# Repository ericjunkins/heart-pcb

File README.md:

# heart-pcb

## Project Information
Heart PCB is a device that uses a STM8S003K3 Microchip to do bit-level control of a set of LEDs to display an input message in half-byte binary

### Software utilites
#### STM8S003K3 Programming

Programming of the STM8S003K3 was done using ST Visual Develop (STVD) and utilized ST Visual Programming (STVP). In addition it requires the Cosmic Compilier software.

> https://www.st.com/en/development-tools/stvd-stm8.html

> https://www.st.com/content/st_com/en/products/development-tools/software-development-tools/stm8-software-development-tools/stm8-programmers/stvp-stm8.html

> http://www.cosmicsoftware.com/download.php

I initially followed along with the STM8SVLDISCOVERY discovery board tutorial to program the STM8S003K3

> https://www.st.com/content/ccc/resource/technical/document/user_manual/53/20/92/c8/ad/57/45/e8/DM00040678.pdf/files/DM00040678.pdf/jcr:content/translations/en.DM00040678.pdf

#### PCB Development

The printed circuit board was designed using KiCAD, the Gerber files can be found at 

> [Gerber File Location](Gerbers/)

## Technical Information
### PCB Development

#### Electrical Schematic 

#### PCB Board Layout

### Software Development

The STM8S003K3 MCU is programmed to blink the 4 display LEDS(2-5) to display a message in half-bit binary at 0.5 Hz frequency. Below is an explaination on how it does this.

* Loop through the char * message and look at each individual char. 
* Each char is an 8 bit sequence, which will first be broken down into a "high byte" and "low byte". These are really a high half-byte and low half-byte as they are only 4 bits each. 
* The high byte and low byte will be switched, because humans read binary starting at the 0th bit, which is the right most bit, so we will want to switch high/low to make more sense to us
* These are now inserted into a bitArray, which is of length 2*length(message)

* Once the bitArray is fully built it proceeds to the main loop of LED control
* Each element of the bitArray is taken and each individual bit is then used to turn on/off an LED. Again because humans read right o left the LED1 (left-most on the PCB) corresponds to bit0, and LED4 (right-most on the PCB) corresponds to bit3

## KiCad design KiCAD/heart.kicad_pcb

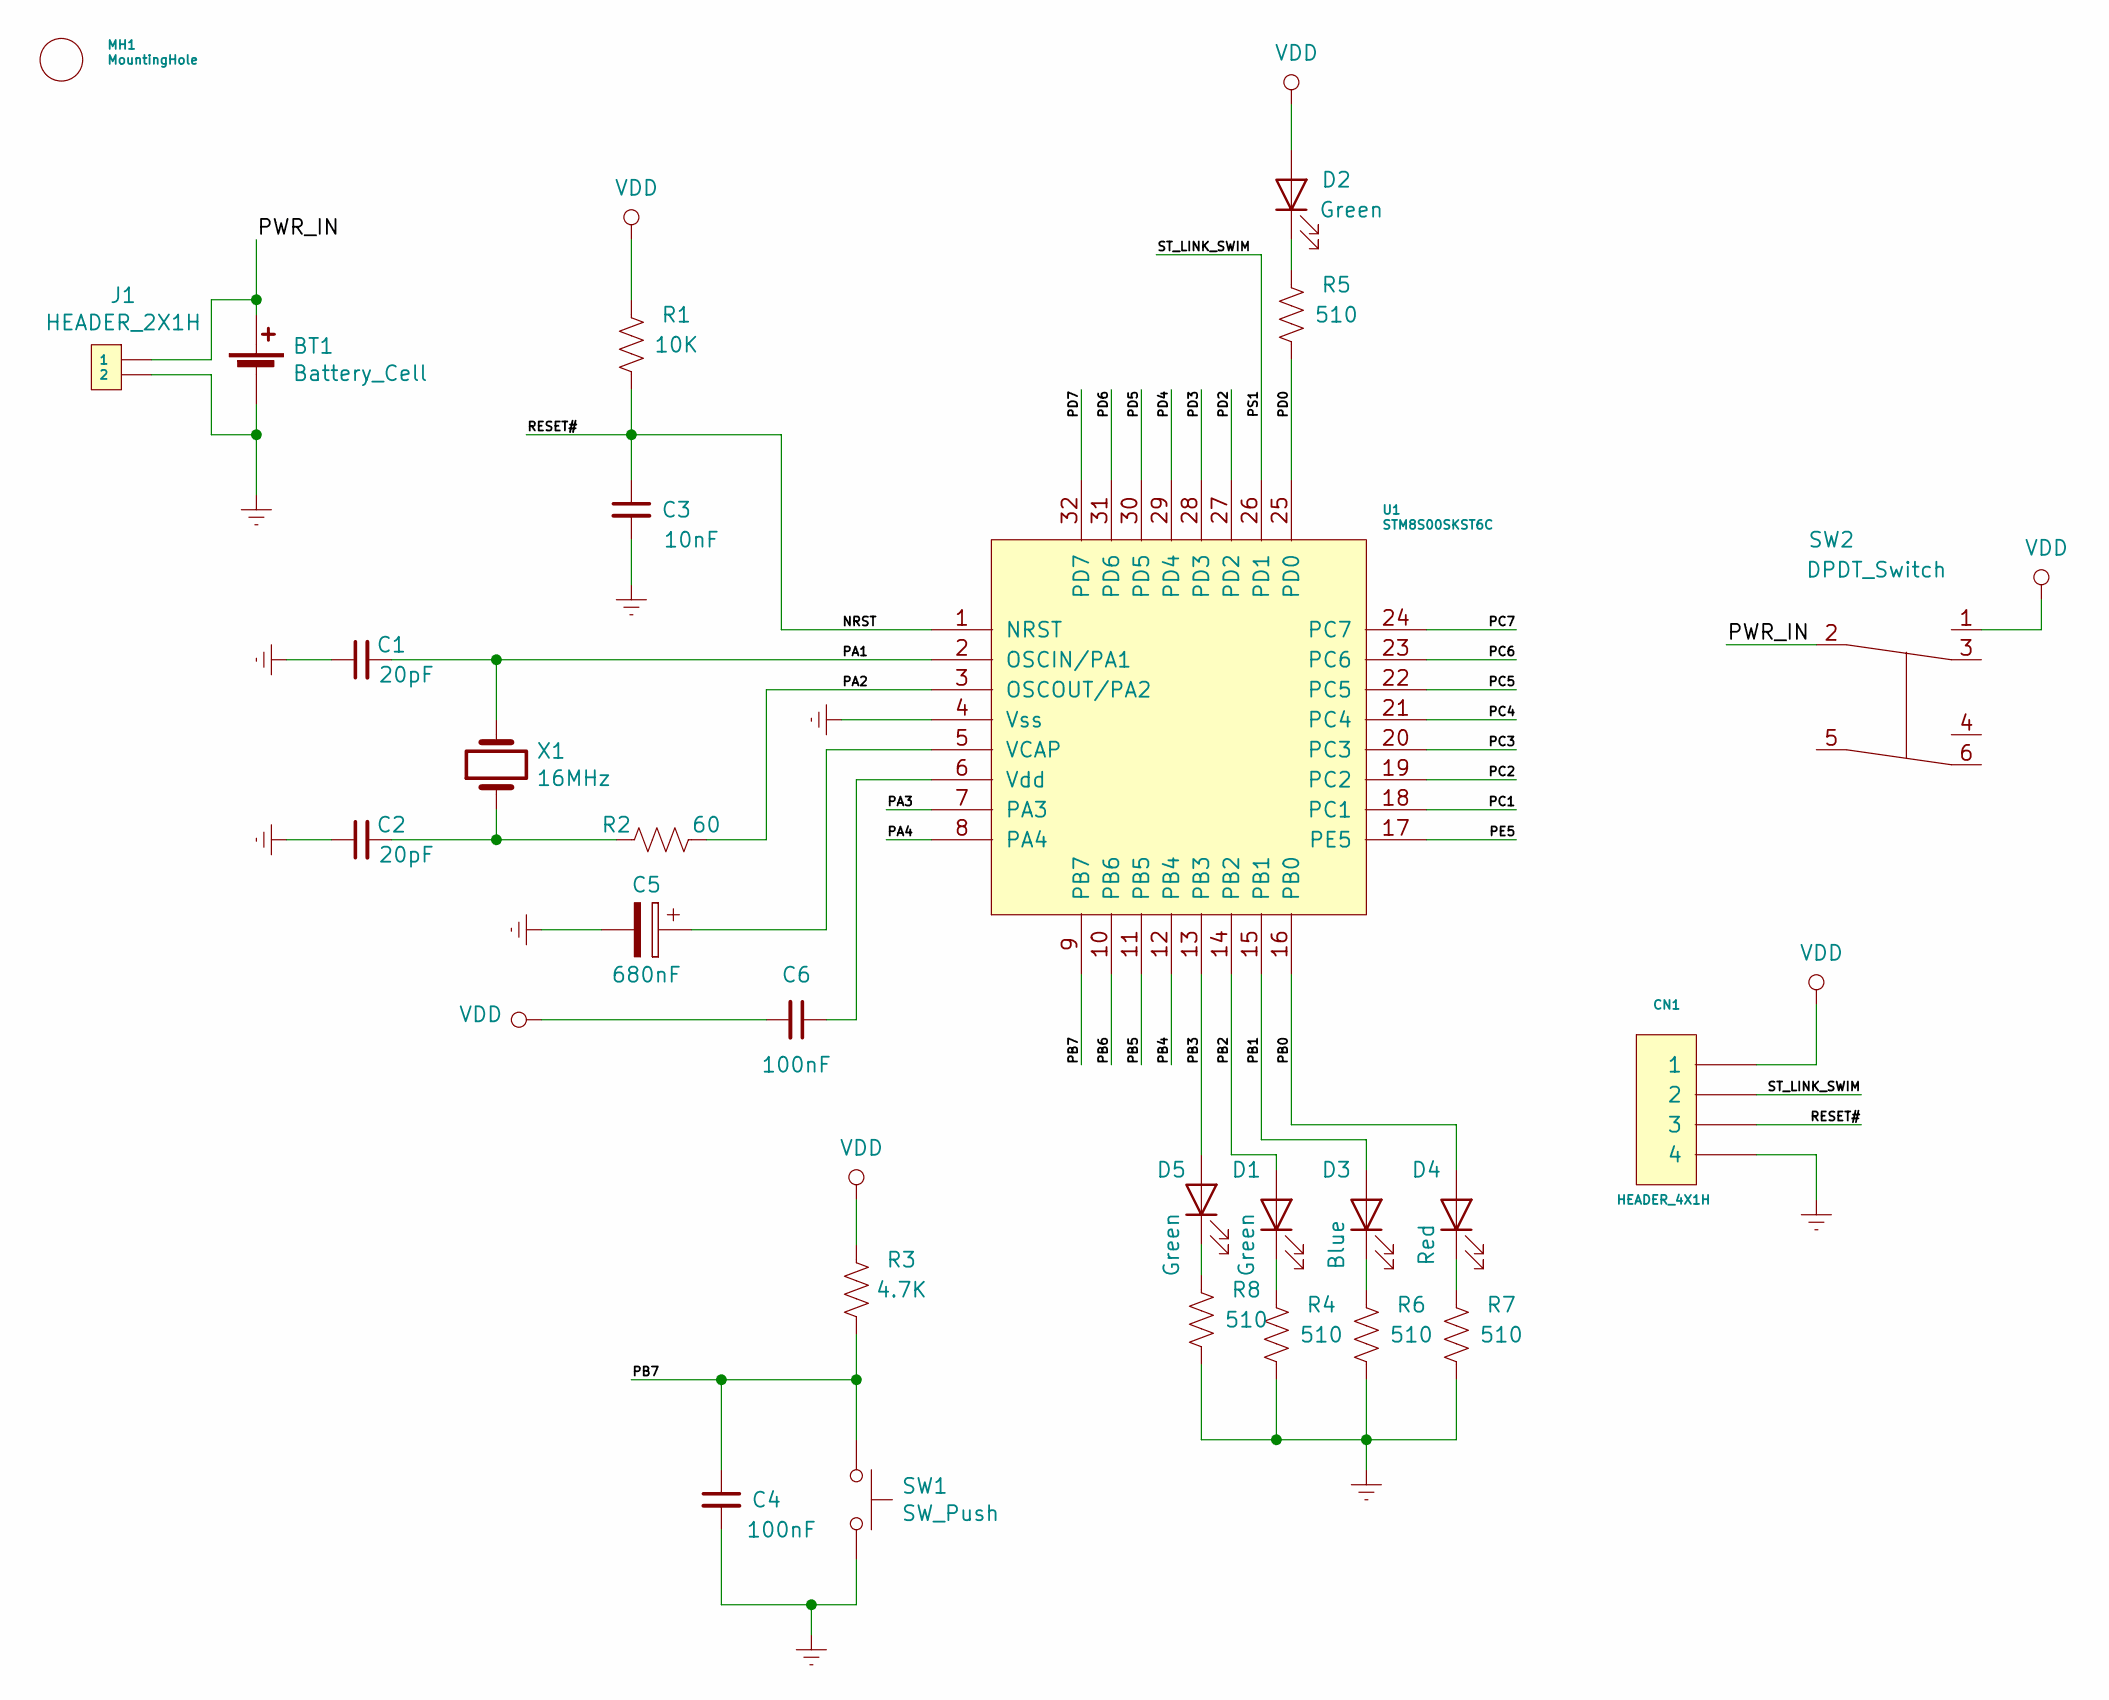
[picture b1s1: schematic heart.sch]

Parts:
BT1: Battery_Cell; SMD 12MM Coin Battery Retainer
C1, C2: 20pF; C_0805_2012Metric
C3: 10nF; C_0805_2012Metric
C4, C6: 100nF; C_0805_2012Metric
C5: 680nF; CP_Elec_6.3x5.9
CN1: HEADER_4X1H
D1, D2, D5: Green; LED_0805_2012Metric
D3: Blue; LED_0805_2012Metric
D4: Red; LED_0805_2012Metric
J1: HEADER_2X1H
MH1: MountingHole; keychain_hole
R1: 10K; R_0805_2012Metric
R2: 60; R_0805_2012Metric
R3: 4.7K; R_0805_2012Metric
R4, R5, R6, R7, R8: 510; R_0805_2012Metric
SW1: SW_Push; HEADER_2X1H
SW2: DPDT_Switch; 732-10145-1-ND DPDT Slide Switch
U1: STM8S00SKST6C; LQFP-32_7x7mm_P0.8mm
X1: 16MHz; Crystal_SMD_HC49-SD

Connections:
/NRST: C3.1, CN1.3, R1.1, U1.1 (NRST)
/PA1: C1.2, U1.2 (OSCIN/PA1), X1.2
/PA2: R2.2, U1.3 (OSCOUT/PA2)
/PA3: U1.7 (PA3)
/PA4: U1.8 (PA4)
/PB0: D4.2 (A), U1.16 (PB0)
/PB1: D3.2 (A), U1.15 (PB1)
/PB2: D1.2 (A), U1.14 (PB2)
/PB3: D5.2 (A), U1.13 (PB3)
/PB4: U1.12 (PB4)
/PB5: U1.11 (PB5)
/PB6: U1.10 (PB6)
/PB7: C4.1, R3.1, SW1.1, U1.9 (PB7)
/PC1: U1.18 (PC1)
/PC2: U1.19 (PC2)
/PC3: U1.20 (PC3)
/PC4: U1.21 (PC4)
/PC5: U1.22 (PC5)
/PC6: U1.23 (PC6)
/PC7: U1.24 (PC7)
/PD0: R5.1, U1.25 (PD0)
/PD2: U1.27 (PD2)
/PD3: U1.28 (PD3)
/PD4: U1.29 (PD4)
/PD5: U1.30 (PD5)
/PD6: U1.31 (PD6)
/PD7: U1.32 (PD7)
/PE5: U1.17 (PE5)
/PS1: CN1.2, U1.26 (PD1)
/PWR_IN: BT1.1 (+), J1.1, SW2.2
Earth: BT1.2 (-), C1.1, C2.1, C3.2, C4.2, C5.2, CN1.4, J1.2, R4.1, R6.1, R7.1, R8.1, SW1.2, U1.4 (Vss)
unnamed: C2.2, R2.1, X1.1
unnamed: C5.1, U1.5 (VCAP)
unnamed: C6.1, U1.6 (Vdd)
unnamed: D1.1 (K), R4.2
unnamed: D2.1 (K), R5.2
unnamed: D3.1 (K), R6.2
unnamed: D4.1 (K), R7.2
unnamed: D5.1 (K), R8.2
VDD: C6.2, CN1.1, D2.2 (A), R1.2, R3.2, SW2.1

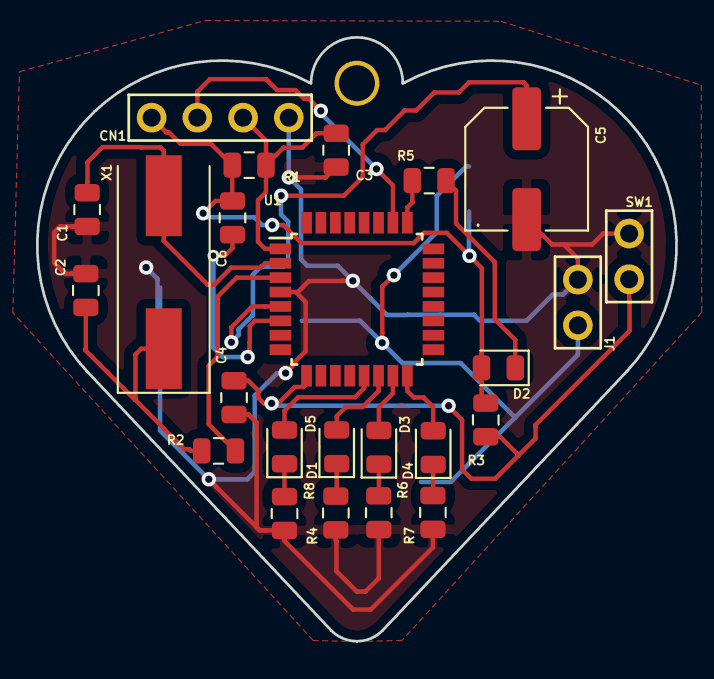
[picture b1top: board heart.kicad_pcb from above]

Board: 2 copper layers, 35.5 x 33.5 mm, 27 parts (0 on the bottom side), 21 nets.

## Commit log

2019-02-03 Initial commit of information
2019-02-03 Adding KiCAD files, and current test code to run the STM8S003K3
2019-02-03 adding images
2019-02-03 updating images
2019-02-03 updating readme
2019-02-03 fixing type in readme
2019-02-03 updating readame
2019-02-13 Adding main header file and update schematic
